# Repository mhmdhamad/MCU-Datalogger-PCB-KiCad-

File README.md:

# MCU Datalogger — KiCad PCB Project

An MCU-based datalogger board designed in KiCad 9, featuring a real-time clock (DS1337S) and onboard memory, built around an ATmega328P-AU.

## Branches

This repository uses branches to track different hardware revisions of the same design:

| Branch    | Description                                  |
|-----------|-----------------------------------------------|
| `main`    | Primary development branch                    |
| `2layer`  | 2-layer PCB variant                            |
| `4layer`  | 4-layer PCB variant (dedicated ground/power planes) |

Each branch contains its own schematic and PCB layout for that board revision. Gerbers for each variant are generated and stored per-branch.

## Features

- ATmega328P-AU microcontroller
- DS1337S real-time clock
- GPIO and serial header breakouts
- Designed and routed in KiCad 9.0

## Getting Started

1. Clone the repository:
   ```
   git clone https://github.com/mhmdhamad/MCU-Datalogger-PCB-KiCad-.git
   ```
2. Check out the branch for the board revision you want:
   ```
   git checkout 2layer
   ```
3. Open `MCU Datalogger.kicad_pro` in KiCad 9.0 or later.

## License

This project is licensed under the [CERN Open Hardware Licence Version 2 - Strongly Reciprocal (CERN-OHL-S)](LICENSE). You are free to use, study, modify, and manufacture this design, provided that any distributed modifications are released under the same license.

## Author

Mohammad — MSc Electronics Engineering, Lebanese International University

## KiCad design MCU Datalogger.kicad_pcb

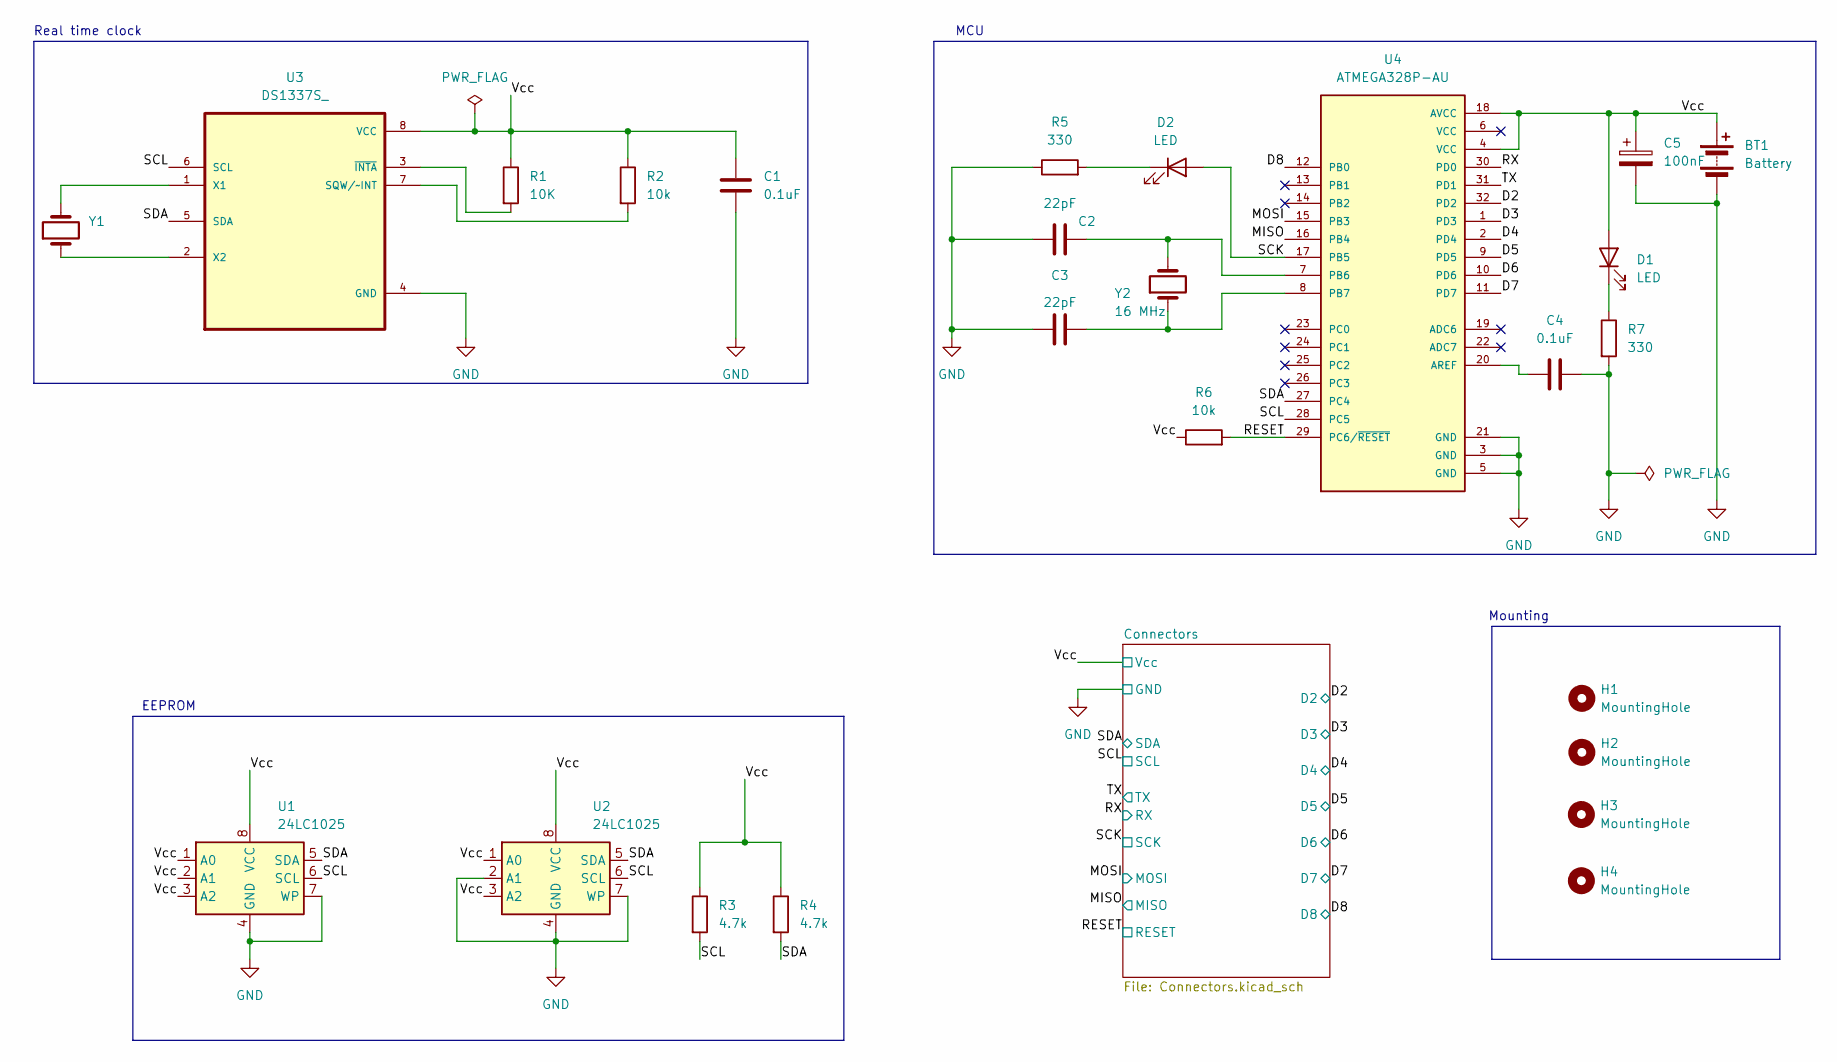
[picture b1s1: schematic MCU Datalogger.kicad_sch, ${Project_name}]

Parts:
BT1: Battery; PinHeader_1x02_P2.54mm_Vertical
C1, C4: 0.1uF; C_0805_2012Metric
C2, C3: 22pF; C_0805_2012Metric
C5: 100nF; C_0805_2012Metric
D1, D2: LED; LED_0805_2012Metric
H1, H2, H3, H4: MountingHole; MountingHole_2.1mm
R1: 10K; R_0805_2012Metric
R2, R6: 10k; R_0805_2012Metric
R3, R4: 4.7k; R_0805_2012Metric
R5, R7: 330; R_0805_2012Metric
U1, U2: 24LC1025; SOIC-8_5.3x5.3mm_P1.27mm
U3: DS1337S_; SOIC127P600X175-8N
U4: ATMEGA328P-AU; QFP80P900X900X120-32N; PARTREV 8271A
Y1: 32.768 KHz; Crystal_SMD_5032-2Pin_5.0x3.2mm
Y2: 16 MHz; Crystal_SMD_5032-2Pin_5.0x3.2mm

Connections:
/D2: U4.32 (PD2); also elsewhere on the board
/D3: U4.1 (PD3); also elsewhere on the board
/D4: U4.2 (PD4); also elsewhere on the board
/D5: U4.9 (PD5); also elsewhere on the board
/D6: U4.10 (PD6); also elsewhere on the board
/D7: U4.11 (PD7); also elsewhere on the board
/D8: U4.12 (PB0); also elsewhere on the board
/MISO: U4.16 (PB4); also elsewhere on the board
/MOSI: U4.15 (PB3); also elsewhere on the board
/RESET: R6.2, U4.29 (PC6/~RESET); also elsewhere on the board
/RX: U4.30 (PD0); also elsewhere on the board
/SCK: D2.2 (A), U4.17 (PB5); also elsewhere on the board
/SCL: R3.2, U1.6 (SCL), U2.6 (SCL), U3.6 (SCL), U4.28 (PC5); also elsewhere on the board
/SDA: R4.2, U1.5 (SDA), U2.5 (SDA), U3.5 (SDA), U4.27 (PC4); also elsewhere on the board
/TX: U4.31 (PD1); also elsewhere on the board
/Vcc: BT1.1 (+), C1.1, C5.1, D1.2 (A), R1.1, R2.1, R3.1, R4.1, R6.1, U1.1 (A0), U1.2 (A1), U1.3 (A2), U1.8 (VCC), U2.1 (A0), U2.3 (A2), U2.8 (VCC), U3.8 (VCC), U4.4 (VCC), U4.18 (AVCC); also elsewhere on the board
GND: BT1.2 (-), C1.2, C2.1, C3.1, C4.2, C5.2, R5.1, R7.2, U1.4 (GND), U1.7 (WP), U2.2 (A1), U2.4 (GND), U2.7 (WP), U3.4 (GND), U4.3 (GND), U4.5 (GND), U4.21 (GND); also elsewhere on the board
unnamed: D1.1 (K), R7.1
unnamed: D2.1 (K), R5.2
unnamed: R2.2, U3.7 (SQW/~INT)
unnamed: U3.1 (X1), Y1.2
unnamed: U3.2 (X2), Y1.1
unnamed: R1.2, U3.3 (~INTA)
unnamed: C4.1, U4.20 (AREF)
unnamed: C2.2, U4.7 (PB6), Y2.2
unnamed: C3.2, U4.8 (PB7), Y2.1

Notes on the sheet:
EEPROM
Mounting
MCU
Real time clock

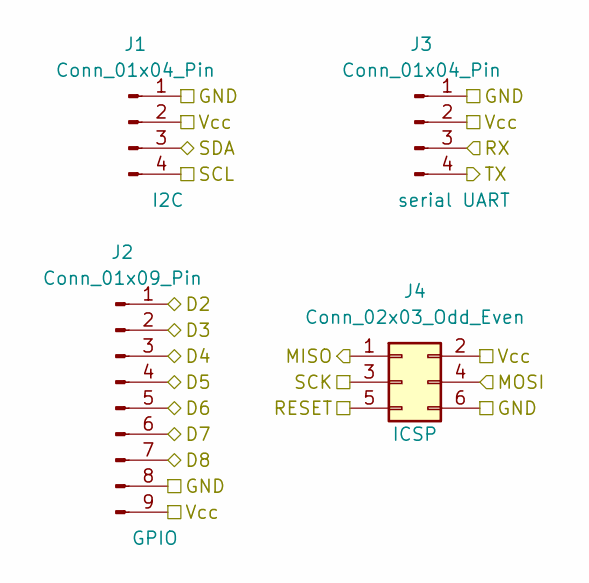
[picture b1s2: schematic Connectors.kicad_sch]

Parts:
J1, J3: Conn_01x04_Pin; PinHeader_1x04_P2.54mm_Vertical
J2: Conn_01x09_Pin; PinHeader_1x09_P2.54mm_Vertical
J4: Conn_02x03_Odd_Even; PinHeader_2x03_P2.54mm_Vertical

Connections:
/D2: J2.1; also elsewhere on the board
/D3: J2.2; also elsewhere on the board
/D4: J2.3; also elsewhere on the board
/D5: J2.4; also elsewhere on the board
/D6: J2.5; also elsewhere on the board
/D7: J2.6; also elsewhere on the board
/D8: J2.7; also elsewhere on the board
/MISO: J4.1; also elsewhere on the board
/MOSI: J4.4; also elsewhere on the board
/RESET: J4.5; also elsewhere on the board
/RX: J3.3; also elsewhere on the board
/SCK: J4.3; also elsewhere on the board
/SCL: J1.4; also elsewhere on the board
/SDA: J1.3; also elsewhere on the board
/TX: J3.4; also elsewhere on the board
/Vcc: J1.2, J2.9, J3.2, J4.2; also elsewhere on the board
GND: J1.1, J2.8, J3.1, J4.6; also elsewhere on the board

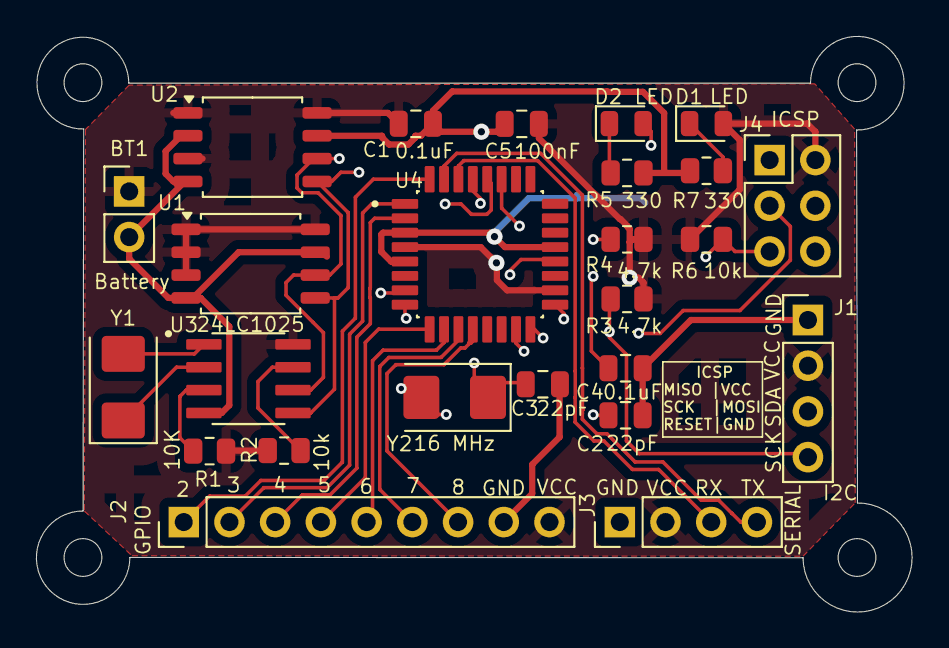
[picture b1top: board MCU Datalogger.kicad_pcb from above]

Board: 4 copper layers, 48.6 x 32.0 mm, 29 parts (0 on the bottom side), 26 nets.
